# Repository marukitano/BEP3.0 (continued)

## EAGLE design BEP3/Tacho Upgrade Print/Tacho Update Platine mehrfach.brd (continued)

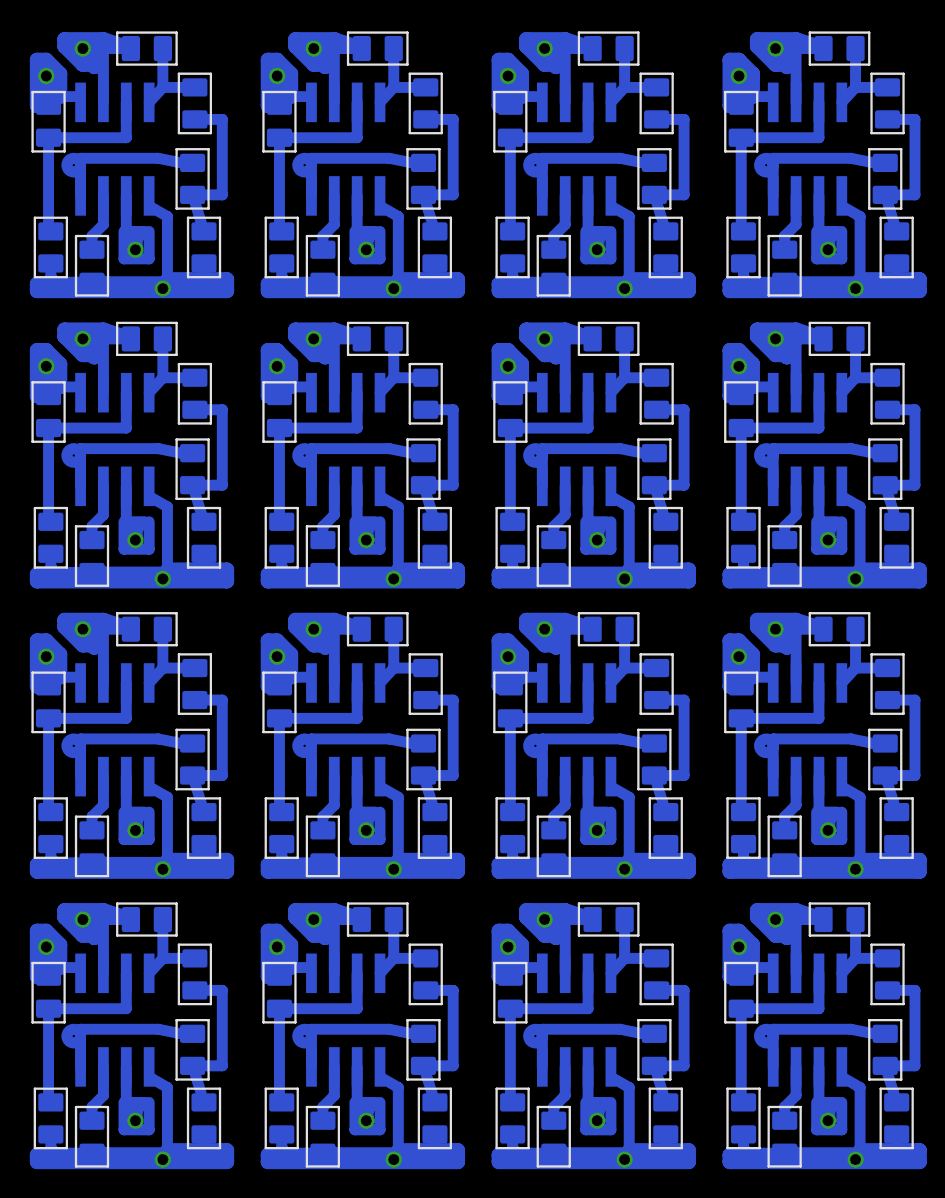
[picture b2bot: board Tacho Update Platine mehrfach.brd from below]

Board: 2 copper layers, 128 parts (128 on the bottom side), 98 nets.
